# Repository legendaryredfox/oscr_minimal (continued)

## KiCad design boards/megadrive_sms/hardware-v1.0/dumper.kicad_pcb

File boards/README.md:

# boards/ — variantes de hardware

Cada pasta é uma versão mínima de hardware do OSCR, em shield para Arduino Mega 2560 R3, só USB (sem LCD, SD e RTC). Firmware, `host/` e `gui/` (raiz) são comuns; o que muda entre as placas são os slots e a pinagem.

| Pasta | Slots | Estado |
|---|---|---|
| [`16_bits/`](16_bits/) | SNES, Mega Drive | Projeto KiCad derivado da `16_and_8_bits`, 108 × 86 mm. **Versões v1.0, v1.2 (sem TVS) e v1.3 (seletor de tensão, sem TVS nem resistores de 470 Ω), D128, D139 e D140.** Gerbers v. 1.2 (D87: `/CART` no D50, C5 e C6, pontos de teste a 2,54 mm, D99) e v1.0 (a antiga `rev2`: alimentação em 0,8 mm, D97; o zip da v1.0 original, com trilhas de 0,3 mm, saiu do repositório em D110) |
| [`megadrive/`](megadrive/) | Mega Drive | Projeto KiCad criado de `16_bits` (D92), slot no centro, 107 × 65 mm, gerbers v1.1 gerados. **v1.1 com o seletor de tensão 3,3 V/5 V (D138).** Nada encomendado |
| [`snes/`](snes/) | SNES | Projeto KiCad criado de `16_bits` (D93), PIC12F629 em soquete, 107 × 65 mm, só a v1.0 (o SA-1 precisa de 5 V: sem seletor). Nada encomendado |
| [`nes/`](nes/) | NES | Projeto KiCad criado da `16_and_8_bits` (D95), Si5351 sem PIC, 110 × 65 mm, gerbers v1.1 gerados. Famicom em `famicom/` ou `famicom_nes/`. **v1.1 com o seletor de tensão 3,3 V/5 V (D138).** Nada encomendado |
| [`famicom/`](famicom/) | Famicom | Projeto KiCad criado da `16_and_8_bits` (D98), sem Si5351 nem PIC, 107 × 65 mm, gerbers v1.1 gerados. **v1.1 com o seletor de tensão 3,3 V/5 V (D138).** Nada encomendado |
| [`famicom_nes/`](famicom_nes/) | Famicom e NES | Projeto KiCad criado da `16_and_8_bits` (D100), Si5351 sem PIC, 117 × 79 mm (D124), gerbers v1.1 gerados. **v1.1 com o seletor de tensão 3,3 V/5 V (D138).** Nada encomendado |
| [`16_and_8_bits/`](16_and_8_bits/) | SNES, NES, Famicom, Mega Drive, GBA | Projeto KiCad pronto, 144 × 118 mm (v1.0, mínima com fusível) e 144 × 134 mm (**v1.1 com o seletor de tensão 3,3 V/5 V nos slots NES, Famicom e Mega Drive**, D157). Nada encomendado |
| [`megadrive_sms/`](megadrive_sms/) | Mega Drive, Master System | Projeto KiCad criado da `megadrive` v1.0 (D136), 107,1 × 83,1 mm, **v1.0 sem o bloco de troca**, gerbers v1.0 gerados. Nada encomendado. Pendências: direção da etiqueta do SMS, núcleo SMS no firmware |
| [`8_bits/`](8_bits/) | NES, Famicom, Master System | Projeto KiCad criado da `famicom_nes` com o slot SMS da `megadrive_sms` (D153), 117,1 × 97,1 mm (v1.0, mínima com fusível) e 117,1 × 109,1 mm (v1.1, com o seletor de tensão). Nada encomendado |
| [`gb_gba/`](gb_gba/) | GBA; GB e GBC por adaptador | Projeto KiCad criado de `16_and_8_bits` (D94), 138 × 67 mm, gerbers v1.0 gerados. Nada encomendado |
| [`n64/`](n64/) | N64 | Projeto KiCad criado da `16_and_8_bits` (D121), 3,3 V, Si5351 só para a EEPROM, 110,1 × 65,1 mm, só a v1.0 (placa de 3,3 V: sem seletor). Nada encomendado |
| [`completa/`](completa/) | SNES, NES, Famicom, Mega Drive, Master System, N64 e GBA | Projeto KiCad criado da `16_and_8_bits` com os slots SMS e N64 acrescentados (D156), 144,2 × 152,2 mm (v1.0, mínima com fusível) e 144,2 × 168,2 mm (v1.1, com o seletor de tensão nos slots de 5 V, menos o SNES). O N64 está desligado no firmware. Nada encomendado |
| [`_lib/`](_lib/) | Símbolos e footprints compartilhados | Em uso por todas as placas com projeto KiCad |

Cada placa com projeto tem um `render.png` (render 3D do KiCad, vista de cima, da versão mais nova) e, **dentro da pasta de cada versão** (`hardware-v1.0/` etc.), `render-cima.png` e `render-baixo.png` (1768 × 1064, print do render 3D do KiCad) ao lado do `README.md` da versão; refazer com `tools/render_board.sh <placa> <versões...>` e `docs/componentes-opcionais.md`: peças que podem ficar sem montar, o que deixa de funcionar e quais cartuchos são afetados.

## Troca de cartucho, F1 e seletor de tensão (D138, D139)

O 5V dos slots **não é cortado por software** em nenhuma placa: o bloco de troca de cartucho (Q1, Q2, Q3, LEDs verde e amarelo, D19 e D53; D126 a D128) foi retirado em D139. Para trocar o cartucho, **desligue o USB**. Ficaram o F1 (suporte de fusível 5×20 mm de 500 mA, em todas as versões), e nas v1.1 com slot de 5 V o seletor 3,3 V/5 V, o jumper J1 "TRAVA 3,3 V" e os resistores de 470 Ω em série. Circuito e peças: [`docs/referencia/seletor-tensao.md`](../docs/referencia/seletor-tensao.md).

## Como os esquemáticos são desenhados

Para leitura humana (D122): os circuitos locais (LED, resistores, capacitores, Si5351, PIC, regulador, pull-ups) têm **fios diretos** entre os pinos; a alimentação usa **símbolos** `+5V`, `+3V3`, `+5V_CART` e `GND`; **rótulos de net só nos barramentos longos** entre o Mega e os slots. As folhas são geradas por `tools/sch/regen.py` (preserva peças, referências e UUIDs, só refaz o desenho); `tools/sch/verify.py` confere que a conectividade ficou idêntica e `tools/sch/sync_names.py` alinha os nomes de net do PCB (a geometria não muda).

## Layout de cada variante

```
boards/<variante>/
├── README.md        # slots, estado, decisões próprias
├── hardware-v1.0/   # uma pasta por versão (hardware-v1.1/ ...): projeto KiCad (dumper.kicad_pro/_sch/_pcb, fp-lib-table, sym-lib-table) e README.md da versão
├── fab/             # por versão: gerbers-<versão>/, bom-<versão>.csv e dumper-<versão>-jlcpcb.zip
└── docs/            # pinmap.md, bom.md, montagem.md da variante
```

As tabelas de bibliotecas apontam para `${KIPRJMOD}/../../_lib/`. Pinagem idêntica ao OSCR HW5 continua regra de ouro (`CLAUDE.md`, seção 3). Uma variante nova nasce copiando o esqueleto e gerando o próprio `docs/pinmap.md`; `tools/check_netlist.py` aceita `--board <pasta>` e `tools/export_fab.sh <pasta> <versão>` gera os arquivos da fábrica; `gen_pinmap.py` e os demais scripts gerais de `tools/` apontam para `16_and_8_bits/`. As placas de um sistema só têm scripts próprios em `tools/<placa>/` (receita completa em `boards/nes/README.md` e na D96).

Todas as placas novas (`megadrive`, `snes`, `nes`, `famicom`, `famicom_nes`, `gb_gba`, `n64`) e as v1.1 foram roteadas por autoroteador (na v1.1, o roteamento inteiro foi refeito) e **não foram revisadas à mão no KiCad**; nenhuma foi encomendada, montada ou testada com cartucho.

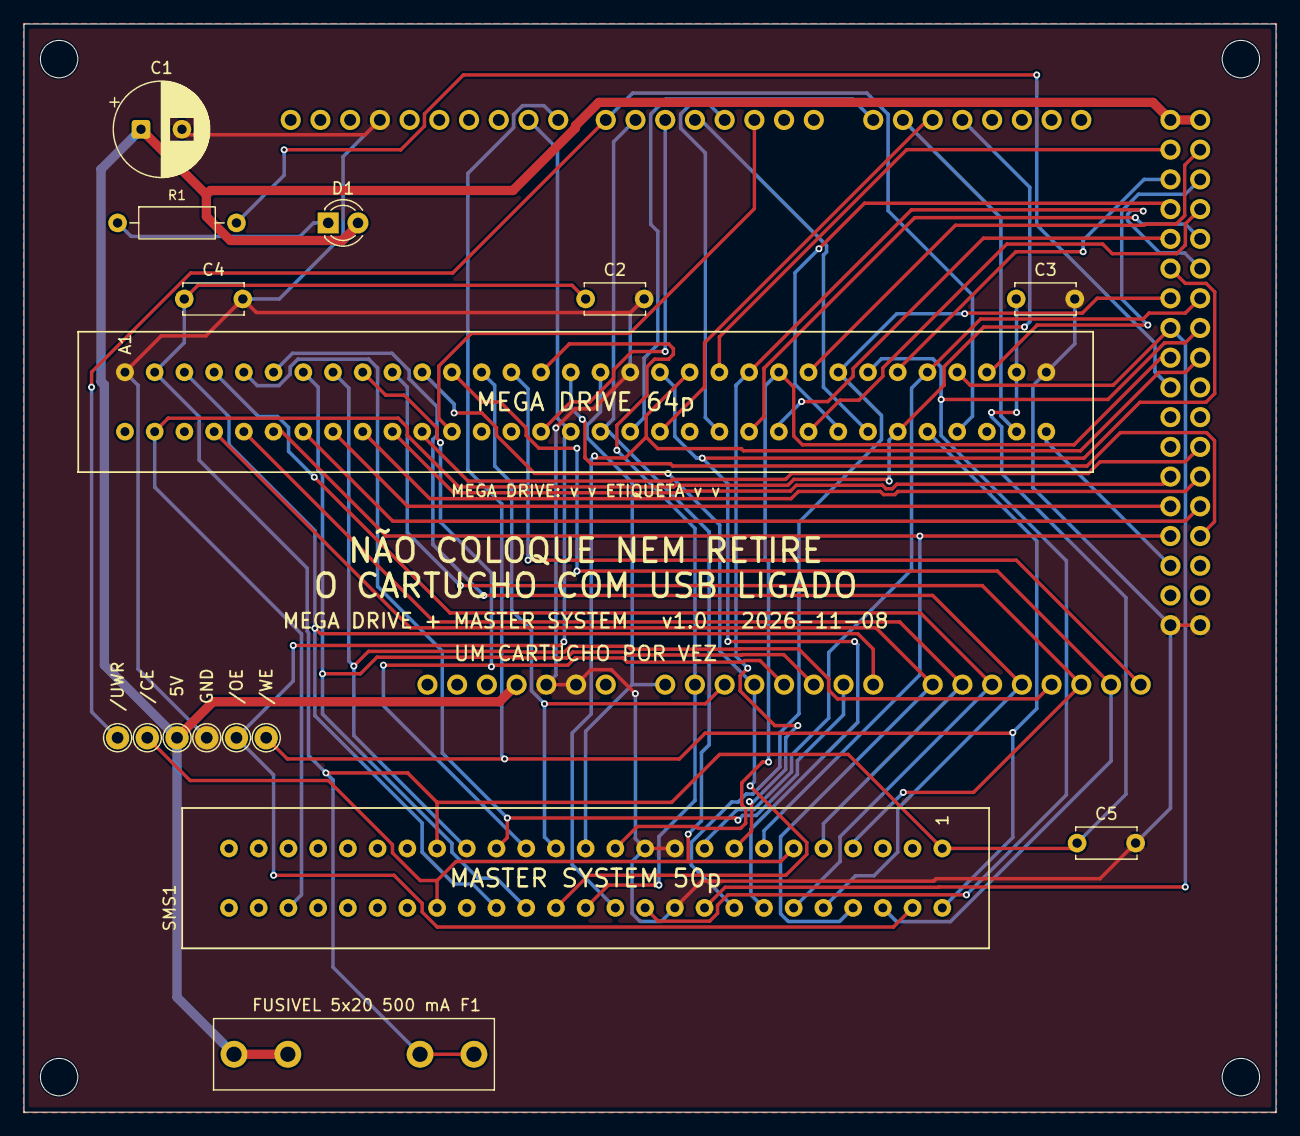
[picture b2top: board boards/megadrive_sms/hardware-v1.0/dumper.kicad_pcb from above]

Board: 2 copper layers, 107.0 x 93.0 mm, 21 parts (0 on the bottom side), 57 nets.

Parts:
A1: Mega2560_R3_Shield
C1: 470u/16V; CP_Radial_D8.0mm_P3.50mm
C2, C3, C4, C5: 100n; C_Disc_D5.0mm_W2.5mm_P5.00mm
D1: LED 3mm; LED_D3.0mm
F1: Fusivel 5x20 500mA; Fuseholder_Littelfuse_100_series_5x20mm
MD1: MD_Slot
MH1, MH2, MH5, MH6: MountingHole_3.2mm; MountingHole_3.2mm_M3
R1: 220R; R_Axial_DIN0207_L6.3mm_D2.5mm_P10.16mm_Horizontal
SMS1: SMS_Slot
TP1: 5V; TestPoint_THTPad_D2.0mm_Drill1.0mm
TP2: GND; TestPoint_THTPad_D2.0mm_Drill1.0mm
TP3: /CE; TestPoint_THTPad_D2.0mm_Drill1.0mm
TP4: /OE; TestPoint_THTPad_D2.0mm_Drill1.0mm
TP5: /WE; TestPoint_THTPad_D2.0mm_Drill1.0mm
TP6: /UWR; TestPoint_THTPad_D2.0mm_Drill1.0mm

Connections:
+5V: A1.5V1, A1.5V3, A1.5V4, C1.1, D1.2, F1.1, TP1.1
+5V_CART: C2.1, C3.1, C4.1, C5.1, F1.2, MD1.A2, MD1.A31, SMS1.1, SMS1.35
/A0: A1.A0, MD1.A17, SMS1.25
/A1: A1.A1, MD1.A15, SMS1.26
/A2: A1.A2, MD1.A13, SMS1.27
/A3: A1.A3, MD1.A11, SMS1.28
/A4: A1.A4, MD1.A9, SMS1.29
/A5: A1.A5, MD1.A7, SMS1.30
/A6: A1.A6, MD1.A5, SMS1.31
/A7: A1.A7, MD1.A3, SMS1.32
/A8: A1.A8, MD1.B4, SMS1.8
/A9: A1.A9, MD1.B5, SMS1.9
/A10: A1.A10, MD1.A4, SMS1.12
/A11: A1.A11, MD1.A6, SMS1.10
/A12: A1.A12, MD1.A8, SMS1.33
/A13: A1.A13, MD1.A10, SMS1.7
/A14: A1.A14, MD1.A12, SMS1.6
/A15: A1.A15, MD1.A14
/CART: A1.D50, MD1.B32
/D2: A1.D2, MD1.B12
/D3: A1.D3, MD1.B21
/D4: A1.D4, MD1.B26
/D5: A1.D5, MD1.B15
/D6: A1.D6, MD1.B17, SMS1.11, SMS1.36, TP3.1
/D7: A1.D7, MD1.B29, TP6.1
/D8: A1.D8, MD1.B28, SMS1.2, TP5.1
/D9: A1.D9, MD1.B16, SMS1.4, TP4.1
/D14: A1.D14, MD1.B18
/D15: A1.D15, MD1.B31
/D16: A1.D16, MD1.B19
/D17: A1.D17, MD1.B2, MD1.B27, SMS1.46
/D22: A1.D22, MD1.A21
/D23: A1.D23, MD1.A24
/D24: A1.D24, MD1.A27
/D25: A1.D25, MD1.A30
/D26: A1.D26, MD1.B25
/D27: A1.D27, MD1.B24
/D28: A1.D28, MD1.B23
/D29: A1.D29, MD1.B22
/D30: A1.D30, MD1.A19, SMS1.14
/D31: A1.D31, MD1.A22, SMS1.15
/D32: A1.D32, MD1.A25, SMS1.16
/D33: A1.D33, MD1.A28, SMS1.17
/D34: A1.D34, MD1.A29, SMS1.18
/D35: A1.D35, MD1.A26, SMS1.22
/D36: A1.D36, MD1.A23, SMS1.23
/D37: A1.D37, MD1.A20, SMS1.24
/D43: A1.D43, MD1.B11
/D44: A1.D44, MD1.B10
/D45: A1.D45, MD1.B9
/D46: A1.D46, MD1.B8
/D47: A1.D47, MD1.B7
/D48: A1.D48, MD1.B6, SMS1.13
/D49: A1.D49, MD1.A16
GND: A1.GND1, A1.GND2, A1.GND3, A1.GND5, A1.GND6, C1.2, C2.2, C3.2, C4.2, C5.2, MD1.A1, MD1.A18, MD1.A32, SMS1.19, SMS1.20, SMS1.21, TP2.1
unnamed: A1.D38, R1.2
unnamed: D1.1, R1.1

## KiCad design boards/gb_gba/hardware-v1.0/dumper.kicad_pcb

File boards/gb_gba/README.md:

# gb_gba — GBA; GB e GBC por adaptador

**README por versão** (renders de cima e de baixo, peças, diferenças): [v1.0](hardware-v1.0/README.md).

Versão mínima de uma função: um slot **GBA** (32 pads SMD, 1,5 mm, **3,3 V**) em shield para Arduino Mega 2560 R3, só USB. GB e GBC entram **só pelo slot GBA, com adaptador** (D56). Um cartucho por vez. Pinagem idêntica ao OSCR HW5 (`docs/pinmap.md`, recorte da `16_and_8_bits`). Sem SD, sem LCD, sem Si5351 e sem PIC.

**Estado:** v1.0, 138,1 × 67,1 mm. ERC com 1 aviso de biblioteca (U1, antes U3; o mesmo da `16_and_8_bits`); DRC sem erros nem ligações abertas (só avisos de biblioteca e paridade); netlist confere com `docs/pinmap.md`; gerbers em `fab/`. Roteada pelo Freerouting (MCP) com o GND junto; o `/D9` o autoroteador não achou caminho em nenhuma tentativa e foi roteado pelo A* de `tools/historico/pcb_v12` (`tools/boards/gb_gba/route_net.py`). **Revisar o layout no KiCad antes de encomendar.** Nada encomendado nem montado. Montagem: `docs/montagem.md`. Trilhas de alimentação (`+5V`, `+3V3`) alargadas até onde cabe, 0,8 mm na maior parte (`tools/historico/revisao/widen_power.py`, D96).

## Diferenças em relação à `16_and_8_bits`

| Item | 16_and_8_bits | gb_gba |
|---|---|---|
| Slots | SNES, NES, Famicom, Mega Drive, GBA | só GBA |
| Regulador 3,3 V (U3, C7, C8, C9; na gb_gba: U1, C2, C3, C4, D109) | sim | sim |
| Si5351, PIC, R2, C2 a C6 | sim | não |
| Placa | 144 × 108 mm | 138,1 × 67,1 mm |
| Furos | 4 M3 de canto, 6 do Mega, 2 M2 do Si5351 | 4 M3 junto ao Mega (nenhum do lado do slot GBA); sem os 6 do Mega |

O slot GBA ficou **na mesma orientação** (boca para a direita, etiqueta para cima), mas encostado no Mega, com as peças soltas dentro da área do Mega. O pino 31 (AUD_IRQ) continua sem ligação (D22).

## Como foi feita

Mesma receita da `megadrive/` e da `snes/` (`boards/megadrive/README.md`, D92 e D93), com `tools/boards/gb_gba/place.py`. `fix_nets.py` leva **um pad por chamada** (num laço de shell).

```
python3 tools/check_netlist.py --board gb_gba
kicad-cli sch erc boards/gb_gba/hardware-v1.0/dumper.kicad_sch
kicad-cli pcb drc boards/gb_gba/hardware-v1.0/dumper.kicad_pcb
tools/export_fab.sh gb_gba v1.0
```

**Peças opcionais:** o que se perde ao retirar cada componente, e que jogos são afetados, está em [`docs/componentes-opcionais.md`](docs/componentes-opcionais.md).

## Versões

Só a **v1.0** (`hardware-v1.0/`; fábrica em `fab/gerbers-v1.0/`, `fab/dumper-v1.0-jlcpcb.zip`, `fab/bom-v1.0.csv`; renders em `hardware-v1.0/render-cima.png` e `render-baixo.png`). Ela já leva o suporte do fusível F1 (D138). O 5V dos slots vai direto do Mega e **não é cortado por software** (o bloco de troca de cartucho, D126 a D128, foi retirado em D139): para trocar o cartucho, desligue o USB. Verificação: `python3 tools/check_netlist.py --board gb_gba`.

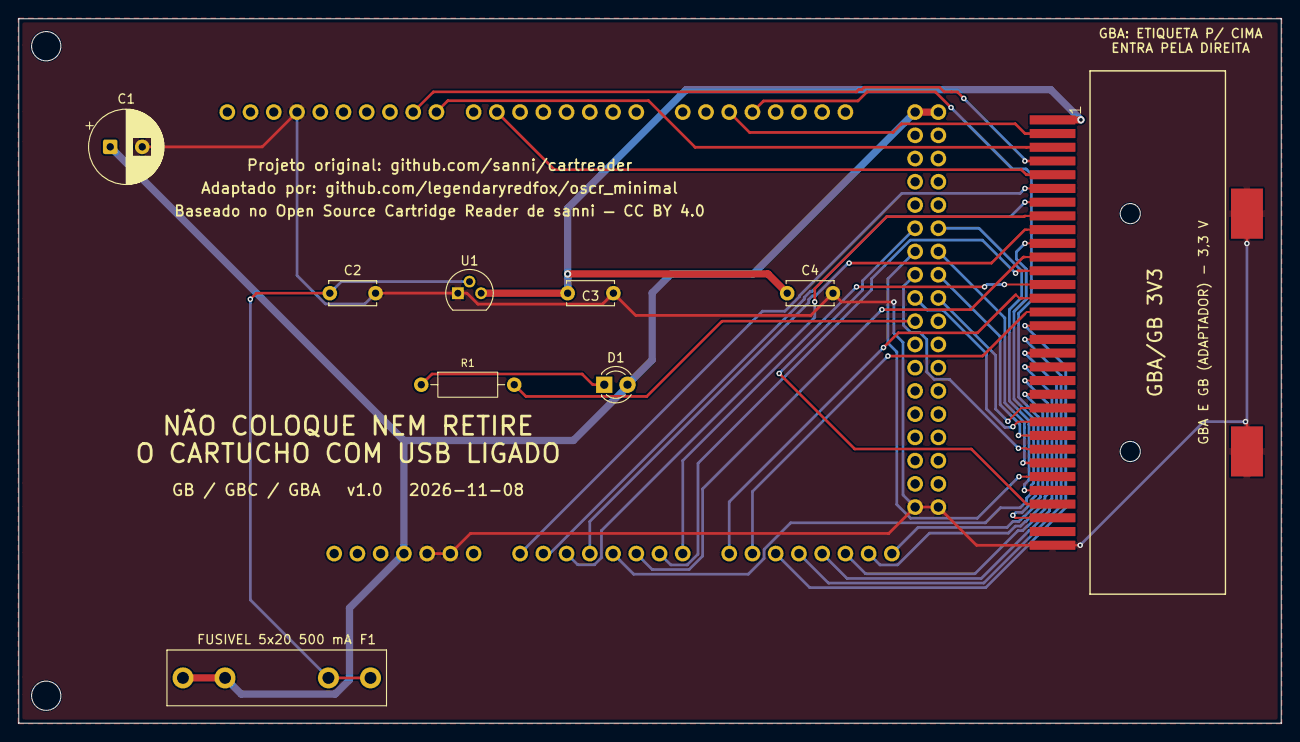
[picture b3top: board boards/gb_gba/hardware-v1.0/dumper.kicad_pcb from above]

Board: 2 copper layers, 138.0 x 77.0 mm, 12 parts (0 on the bottom side), 35 nets.

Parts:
A1: Mega2560_R3_Shield
C1: 470u/16V; CP_Radial_D8.0mm_P3.50mm
C2, C3: 1u; C_Disc_D5.0mm_W2.5mm_P5.00mm
C4: 100n; C_Disc_D5.0mm_W2.5mm_P5.00mm
D1: LED 3mm; LED_D3.0mm
F1: Fusivel 5x20 500mA; Fuseholder_Littelfuse_100_series_5x20mm
GBA1: GBA_Slot
MH1, MH3: MountingHole_3.2mm; MountingHole_3.2mm_M3
R1: 220R; R_Axial_DIN0207_L6.3mm_D2.5mm_P10.16mm_Horizontal
U1: MCP1700-3302E/TO (3,3 V); TO-92

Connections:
+3V3: C3.1, C4.1, GBA1.1, U1.3
+5V: A1.5V1, A1.5V3, A1.5V4, C1.1, D1.2, F1.1
+5V_CART: C2.1, F1.2, U1.2
/A0: A1.A0, GBA1.6
/A1: A1.A1, GBA1.7
/A2: A1.A2, GBA1.8
/A3: A1.A3, GBA1.9
/A4: A1.A4, GBA1.10
/A5: A1.A5, GBA1.11
/A6: A1.A6, GBA1.12
/A7: A1.A7, GBA1.13
/A8: A1.A8, GBA1.14
/A9: A1.A9, GBA1.15
/A10: A1.A10, GBA1.16
/A11: A1.A11, GBA1.17
/A12: A1.A12, GBA1.18
/A13: A1.A13, GBA1.19
/A14: A1.A14, GBA1.20
/A15: A1.A15, GBA1.21
/D6: A1.D6, GBA1.5
/D8: A1.D8, GBA1.3
/D9: A1.D9, GBA1.4
/D16: A1.D16, GBA1.2
/D17: A1.D17, GBA1.30
/D30: A1.D30, GBA1.29
/D31: A1.D31, GBA1.28
/D32: A1.D32, GBA1.27
/D33: A1.D33, GBA1.26
/D34: A1.D34, GBA1.25
/D35: A1.D35, GBA1.24
/D36: A1.D36, GBA1.23
/D37: A1.D37, GBA1.22
GND: A1.GND1, A1.GND2, A1.GND3, A1.GND5, A1.GND6, C1.2, C2.2, C3.2, C4.2, GBA1.32, GBA1.SHIELD_3, GBA1.SHIELD_4, U1.1
unnamed: A1.D38, R1.2
unnamed: D1.1, R1.1

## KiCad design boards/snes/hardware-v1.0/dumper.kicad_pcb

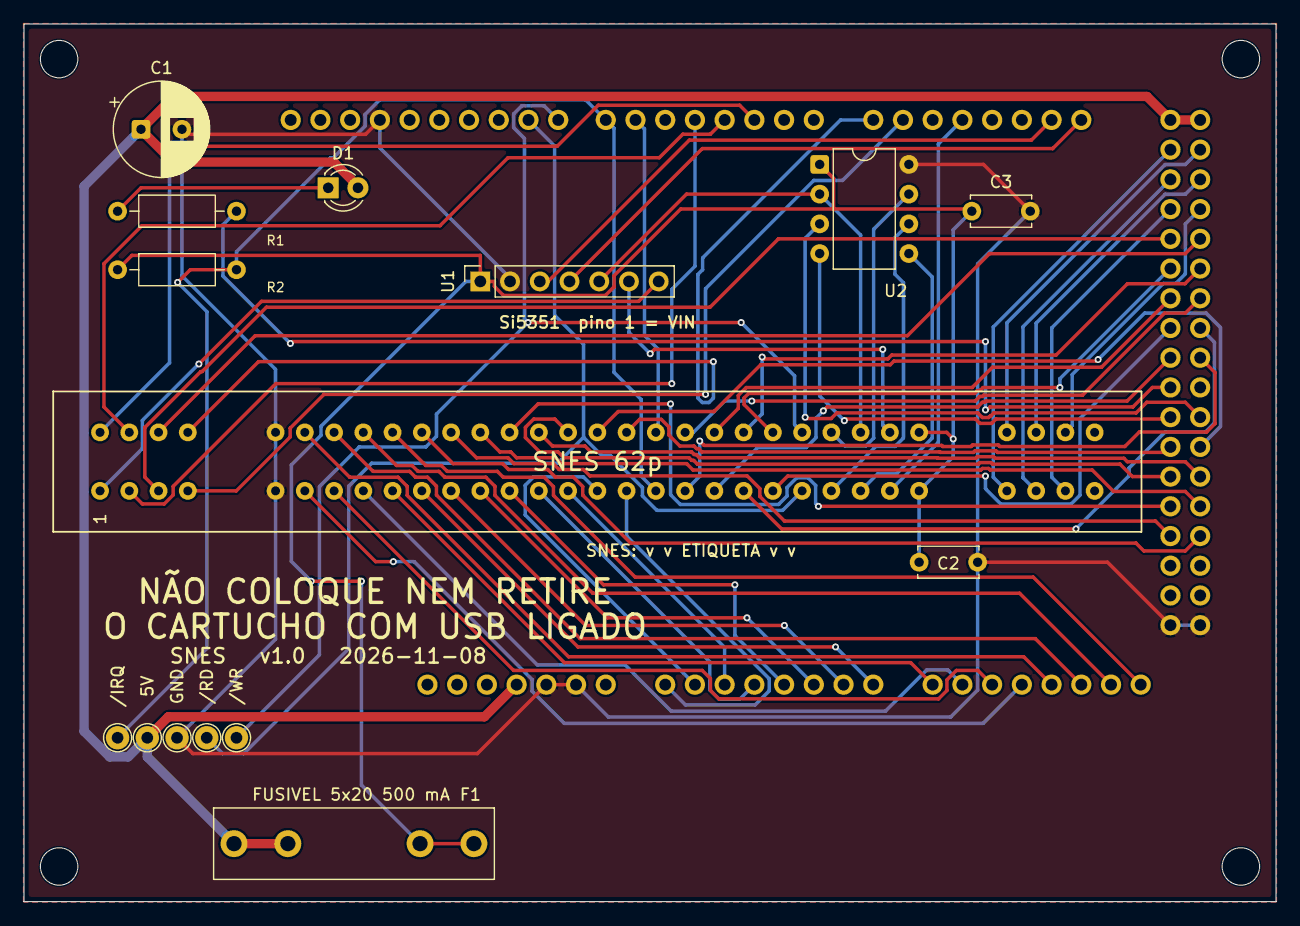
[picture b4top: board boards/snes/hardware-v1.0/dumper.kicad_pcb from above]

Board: 2 copper layers, 107.0 x 75.0 mm, 20 parts (0 on the bottom side), 65 nets.

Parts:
A1: Mega2560_R3_Shield
C1: 470u/16V; CP_Radial_D8.0mm_P3.50mm
C2, C3: 100n; C_Disc_D5.0mm_W2.5mm_P5.00mm
D1: LED 3mm; LED_D3.0mm
F1: Fusivel 5x20 500mA; Fuseholder_Littelfuse_100_series_5x20mm
MH1, MH2, MH3, MH4: MountingHole_3.2mm; MountingHole_3.2mm_M3
R1: 220R; R_Axial_DIN0207_L6.3mm_D2.5mm_P10.16mm_Horizontal
R2: 1k; R_Axial_DIN0207_L6.3mm_D2.5mm_P10.16mm_Horizontal
SNES1: SNES_Slot
TP1: 5V; TestPoint_THTPad_D2.0mm_Drill1.0mm
TP2: GND; TestPoint_THTPad_D2.0mm_Drill1.0mm
TP3: /RD; TestPoint_THTPad_D2.0mm_Drill1.0mm
TP4: /WR; TestPoint_THTPad_D2.0mm_Drill1.0mm
TP5: /IRQ; TestPoint_THTPad_D2.0mm_Drill1.0mm
U1: Si5351_Module; PinSocket_1x07_P2.54mm_Vertical
U2: PIC12F629 (em soquete; snescic-lock-resync); DIP-8_W7.62mm

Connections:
+5V: A1.5V1, A1.5V3, A1.5V4, C1.1, D1.2, F1.1, TP1.1
+5V_CART: C2.1, C3.1, F1.2, R2.1, SNES1.27, SNES1.58, U1.1, U2.1
/A0: A1.A0, SNES1.17
/A1: A1.A1, SNES1.16
/A2: A1.A2, SNES1.15
/A3: A1.A3, SNES1.14
/A4: A1.A4, SNES1.13
/A5: A1.A5, SNES1.12
/A6: A1.A6, SNES1.11
/A7: A1.A7, SNES1.10
/A8: A1.A8, SNES1.9
/A9: A1.A9, SNES1.8
/A10: A1.A10, SNES1.7
/A11: A1.A11, SNES1.6
/A12: A1.A12, SNES1.37
/A13: A1.A13, SNES1.38
/A14: A1.A14, SNES1.39
/A15: A1.A15, SNES1.40
/CIC_DATA_0: SNES1.55, U2.7
/CIC_DATA_1: SNES1.24, U2.6
/CIC_RESET: SNES1.25, U2.5
/CLK0: SNES1.1, U1.7
/CLK1: SNES1.57, U1.6
/CLK2: SNES1.56, U1.5, U2.2
/D2: A1.D2, SNES1.32
/D3: A1.D3, SNES1.33
/D4: A1.D4, SNES1.2
/D6: A1.D6, SNES1.49
/D7: A1.D7, R2.2, SNES1.18, TP5.1
/D8: A1.D8, SNES1.54, TP4.1
/D9: A1.D9, SNES1.23, TP3.1
/D14: A1.D14, SNES1.35
/D15: A1.D15, SNES1.4
/D17: A1.D17, SNES1.26
/D22: A1.D22, SNES1.28
/D23: A1.D23, SNES1.59
/D24: A1.D24, SNES1.29
/D25: A1.D25, SNES1.60
/D26: A1.D26, SNES1.30
/D27: A1.D27, SNES1.61
/D28: A1.D28, SNES1.3
/D29: A1.D29, SNES1.34
/D30: A1.D30, SNES1.53
/D31: A1.D31, SNES1.52
/D32: A1.D32, SNES1.51
/D33: A1.D33, SNES1.50
/D34: A1.D34, SNES1.22
/D35: A1.D35, SNES1.21
/D36: A1.D36, SNES1.20
/D37: A1.D37, SNES1.19
/D42: A1.D42, SNES1.48
/D43: A1.D43, SNES1.47
/D44: A1.D44, SNES1.46
/D45: A1.D45, SNES1.45
/D46: A1.D46, SNES1.44
/D47: A1.D47, SNES1.43
/D48: A1.D48, SNES1.42
/D49: A1.D49, SNES1.41
GND: A1.GND1, A1.GND2, A1.GND3, A1.GND5, A1.GND6, C1.2, C2.2, C3.2, SNES1.5, SNES1.36, TP2.1, U1.2, U2.8
unnamed: A1.D38, R1.2
unnamed: D1.1, R1.1
unnamed: A1.D21, U1.4
unnamed: A1.D20, U1.3
unnamed: A1.D40, U2.4
unnamed: A1.D41, U2.3

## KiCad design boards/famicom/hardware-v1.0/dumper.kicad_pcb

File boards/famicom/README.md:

# famicom — só Famicom

**README por versão** (renders de cima e de baixo, peças, diferenças): [v1.0](hardware-v1.0/README.md), [v1.1](hardware-v1.1/README.md).

Versão mínima de uma função: um slot **Famicom** (60p, 2,54 mm) em shield para Arduino Mega 2560 R3, 100% THT, só USB, **5 V** fixo. Um cartucho por vez. Pinagem idêntica ao OSCR HW5 (`docs/pinmap.md`, recorte da `16_and_8_bits`).

**Sem Si5351 e sem PIC:** o slot Famicom não tem pino de clock nem CIC do SNES; o `pinmap.md` não liga nenhum deles ao slot. A placa é a mais simples de todas: slot, LED, C1 e um capacitor.

**Estado:** v1.1, 107,1 × 65,1 mm (v1.0: 107,1 × 61,1 mm). ERC 0 violações; DRC sem erros nem ligações abertas (só 4 avisos de biblioteca e os de paridade das outras placas); netlist confere com `docs/pinmap.md`; gerbers em `fab/`. Roteada pelo Freerouting (MCP) com GND roteado junto e costurado com vias; alimentação (`+5V`) com 0,8 mm desde o roteamento (padrão de net class `/+5V` já corrigido, D96). **Revisar o layout no KiCad antes de encomendar.** Nada encomendado nem montado. Montagem: `docs/montagem.md`.

**NES:** cartucho de 72 pinos não entra aqui; use `boards/nes/`.

## Diferenças em relação à `16_and_8_bits`

| Item | 16_and_8_bits | famicom |
|---|---|---|
| Slots | SNES, NES, Famicom, Mega Drive, GBA | só Famicom |
| Mantido | LED (D1, R1), C1, C4 (VCC do slot; agora C2, D109) | idem |
| Removido | SNES1, NES1, MD1, GBA1, Si5351 (U1), PIC (U2), R2, regulador U3 e C7, C8, C9, C2, C3, C5, C6, furos M2 | |
| Placa | 144 × 108 mm | 107,1 × 65,1 mm |

O slot fica entre as fileiras de pinos do Mega, no mesmo lugar que o Mega Drive na `megadrive/`. **A v1.0 não tem os 6 furos do Mega** (só os 4 de canto) e o F1 fica entre o slot e o header de baixo do Mega, sem a faixa extra: 107,1 × 61,1 mm (D142). Na v1.1, os 6 furos não metalizados do Mega e os 4 de canto foram mantidos.

Ficam sem ligação no Mega: tudo que só os outros sistemas usam (`D2..D9`, `D14..D17`, `D20`, `D21`, `D29..D34`, `D36`, `D37`, `D40`, `D41`) e os de sempre (`D0`, `D1`, `D10..D13`, `D18`, `D19`, `D39`, `D50..D53`).

## Como foi feita

Mesma receita da `nes/` (`boards/nes/README.md`), com `tools/boards/famicom/place.py`: `strip_sch.py` (SNES1, NES1, MD1, GBA1, U1, U2, R2, U3, C2, C3, C5 a C9), `place.py`, `tools/boards/nes/sync_unconnected.py`, `autoroute` do KiCad MCP com o GND como trilha, depois `add_zones.py`, `stitch.py`, `tools/historico/revisao/widen_power.py` (sem efeito aqui: o 5V já saiu com 0,8 mm) e `fill_zones.py`.

```
python3 tools/check_netlist.py --board famicom
kicad-cli sch erc boards/famicom/hardware-v1.1/dumper.kicad_sch
kicad-cli pcb drc boards/famicom/hardware-v1.1/dumper.kicad_pcb
tools/export_fab.sh famicom v1.0
```

**Peças opcionais:** o que se perde ao retirar cada componente, e que jogos são afetados, está em [`docs/componentes-opcionais.md`](docs/componentes-opcionais.md).

## Versões

| Versão | O que tem | Projeto KiCad | Fábrica | Renders (cima e baixo) |
|---|---|---|---|---|
| v1.0 | F1 (suporte de fusível); 5V direto nos slots; 107,1 × 61,1 mm, sem os 6 furos do Mega (D142) | `hardware-v1.0/` | `fab/gerbers-v1.0/`, `fab/dumper-v1.0-jlcpcb.zip`, `fab/bom-v1.0.csv` | `hardware-v1.0/render-cima.png`, `hardware-v1.0/render-baixo.png` |
| v1.1 | v1.0 mais o seletor de tensão 3,3 V/5 V e o J1 (D138; sem resistores em série, D140) | `hardware-v1.1/` | `fab/gerbers-v1.1/`, `fab/dumper-v1.1-jlcpcb.zip`, `fab/bom-v1.1.csv` | `hardware-v1.1/render-cima.png`, `hardware-v1.1/render-baixo.png` (`render.png` = v1.1, de cima) |

O 5V dos slots **não é cortado por software** em nenhuma versão (o bloco de troca de cartucho, D126 a D128, foi retirado em D139): para trocar o cartucho, desligue o USB. Verificação: `python3 tools/check_netlist.py --board famicom` (v1.1) e `python3 tools/check_netlist.py --board famicom boards/famicom/hardware-v1.0/dumper.kicad_sch` (v1.0).

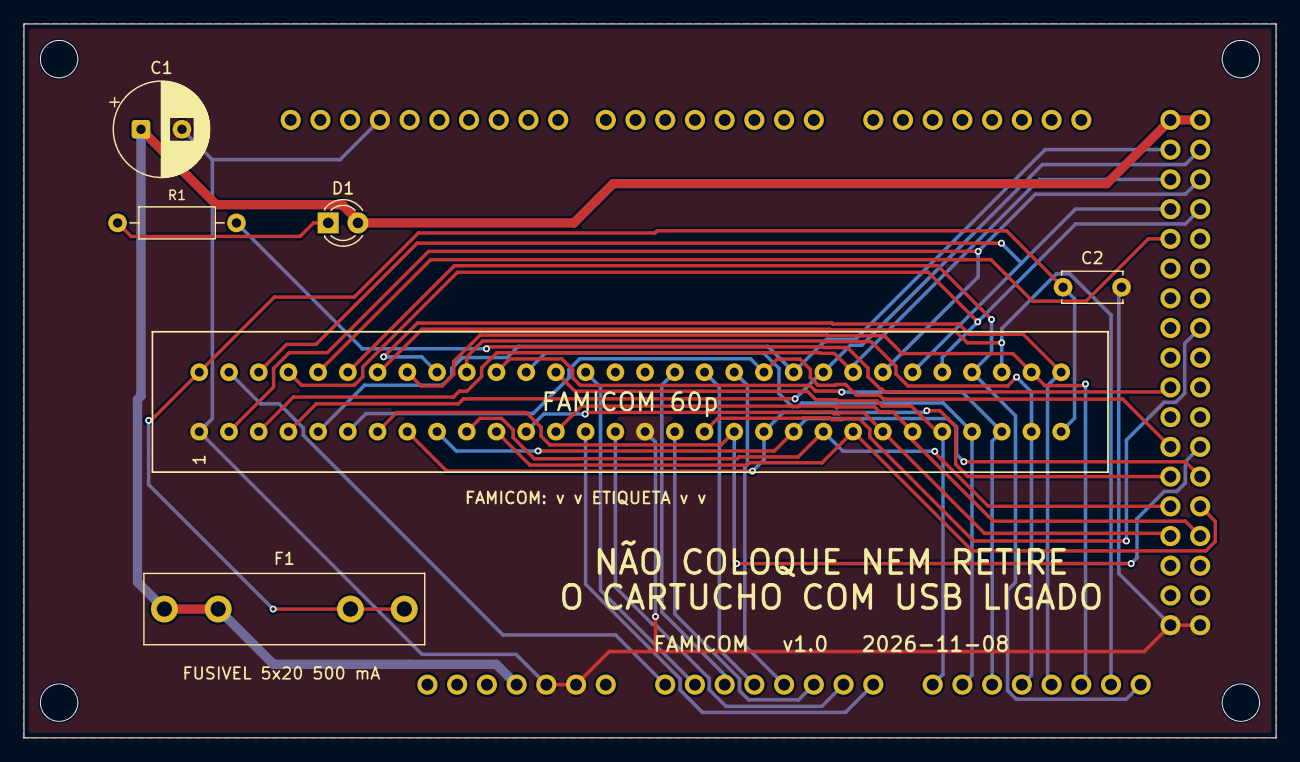
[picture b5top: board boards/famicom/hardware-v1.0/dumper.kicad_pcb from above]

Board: 2 copper layers, 107.0 x 61.0 mm, 11 parts (0 on the bottom side), 37 nets.

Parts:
A1: Mega2560_R3_Shield
C1: 470u/16V; CP_Radial_D8.0mm_P3.50mm
C2: 100n; C_Disc_D5.0mm_W2.5mm_P5.00mm
D1: LED 3mm; LED_D3.0mm
F1: Fusivel 5x20 500mA; Fuseholder_Littelfuse_100_series_5x20mm
FC1: FC_Slot
MH1, MH2, MH3, MH4: MountingHole_3.2mm; MountingHole_3.2mm_M3
R1: 220R; R_Axial_DIN0207_L6.3mm_D2.5mm_P10.16mm_Horizontal

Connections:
+5V: A1.5V1, A1.5V3, A1.5V4, C1.1, D1.2, F1.1
+5V_CART: C2.1, F1.2, FC1.30, FC1.31
/A0: A1.A0, FC1.32
/A1: A1.A1, FC1.44
/A2: A1.A2, FC1.47
/A3: A1.A3, FC1.48
/A4: A1.A4, FC1.49
/A5: A1.A5, FC1.17
/A6: A1.A6, FC1.15
/A7: A1.A7, FC1.14
/A8: A1.A8, FC1.26, FC1.43
/A9: A1.A9, FC1.27, FC1.42
/A10: A1.A10, FC1.28, FC1.41
/A11: A1.A11, FC1.29, FC1.40
/A12: A1.A12, FC1.39, FC1.60
/A13: A1.A13, FC1.38, FC1.59
/A14: A1.A14, FC1.37, FC1.58
/A15: A1.A15, FC1.36, FC1.57
/D22: A1.D22, FC1.5, FC1.51
/D23: A1.D23, FC1.4, FC1.52
/D24: A1.D24, FC1.3, FC1.53
/D25: A1.D25, FC1.2, FC1.54
/D26: A1.D26, FC1.33, FC1.55
/D27: A1.D27, FC1.34, FC1.56
/D28: A1.D28, FC1.35
/D35: A1.D35, FC1.18
/D42: A1.D42, FC1.6, FC1.50
/D43: A1.D43, FC1.7, FC1.19
/D44: A1.D44, FC1.8, FC1.20
/D45: A1.D45, FC1.9, FC1.21
/D46: A1.D46, FC1.10, FC1.22
/D47: A1.D47, FC1.11, FC1.23
/D48: A1.D48, FC1.12, FC1.24
/D49: A1.D49, FC1.13, FC1.25
GND: A1.GND1, A1.GND2, A1.GND3, A1.GND5, A1.GND6, C1.2, C2.2, FC1.1, FC1.16
unnamed: A1.D38, R1.2
unnamed: D1.1, R1.1

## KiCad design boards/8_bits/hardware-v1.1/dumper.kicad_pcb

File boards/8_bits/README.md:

# 8_bits — NES, Famicom e Master System

**README por versão** (renders de cima e de baixo, peças, diferenças): [v1.0](hardware-v1.0/README.md), [v1.1](hardware-v1.1/README.md).

Versão mínima de três slots em shield para Arduino Mega 2560 R3, 100% THT, só USB: **NES** (72p, 2,5 mm), **Famicom** (60p, 2,54 mm) e **Master System / Mark III** (50p, 2,54 mm). Os três slots ficam **em paralelo** nos mesmos pinos do Mega (como no `six_slot_adapter` do OSCR): **um cartucho por vez, em um slot só**. Pinagem idêntica ao OSCR HW5 (`docs/pinmap.md`: NES e Famicom da `famicom_nes`, Master System da `megadrive_sms`).

**Si5351, sem PIC:** o NES usa o `CLK0` do Si5351 no pino 37; Famicom e Master System não usam clock (o pino 47 do SMS fica sem ligação, D136). Sem PIC (CIC do SNES), sem R2 e sem regulador de 3,3 V fixo.

## Versões (regra do usuário, 2026-11-11)

- **v1.0: a mínima que funciona, com fusível.** 5V direto nos slots, atrás do F1 (suporte de fusível 5×20 mm de 500 mA, D144). 117,1 × 97,1 mm.
- **v1.1: proteção mais robusta.** A v1.0 mais o seletor de tensão 3,3 V/5 V nos três slots (LDO LD1117V33, Q1 de bypass, Q2 de comando pelo D18; D138, D147) e o J1 "TRAVA 3,3 V". 117,1 × 109,1 mm. Firmware: ambiente `SerialASCII_Volt`.

O 5V dos slots **não é cortado por software** em nenhuma versão (D139): para trocar o cartucho, desligue o USB.

**Estado:** ERC 0 violações; DRC sem ligações abertas nem erros (só avisos de biblioteca); netlist confere com `docs/pinmap.md` nas duas versões (`tools/check_netlist.py --board 8_bits`). Roteadas pelo Freerouting e costuradas com vias de GND: **revisar o layout no KiCad antes de encomendar**. Nada encomendado, montado nem testado.

## Como foi feita (D153)

Criada da `famicom_nes` (v1.0 para a v1.0, v1.1 para a v1.1) com o slot SMS acrescentado, a mesma receita da `megadrive_sms` (D136). Scripts em `tools/boards/8_bits/` (da raiz do repositório):

1. `add_sms_sch.py` acrescenta SMS1 e o capacitor do slot ao esquemático, tira as marcas de não conexão dos 11 pinos do Mega que só o SMS usa (D6, D8, D9, D17, D30 a D34, D36, D37) e põe os rótulos. Variáveis `SMS_VCC` (`+5V_CART` na v1.0, `VCC_CART` na v1.1), `SMS_CAP` e `SMS_CAP_SRC`.
2. `place_sms.py` (python com `pcbnew`) tira trilhas e zonas, acrescenta SMS1 e o capacitor, liga os pads do Mega às nets novas; na v1.0 estende a placa para baixo (127 para 135 mm).
3. `renum.py` (v1.1) e `renum_pwr.py` deixam as referências em sequência: C4 (SMS), C5 e C6 (LDO), R2 a R4, Q1 e Q2, e os `#PWR` (D109, D150).
4. `reroute.sh` (`VER=v1.0|v1.1`): Freerouting, zonas de GND, costura e preenchimento; depois `tools/troca/pads_solidos.py` onde o DRC acusa `starved_thermal`.

```
python3 tools/check_netlist.py --board 8_bits                                              # v1.1
python3 tools/check_netlist.py --board 8_bits boards/8_bits/hardware-v1.0/dumper.kicad_sch  # v1.0
kicad-cli sch erc boards/8_bits/hardware-v1.1/dumper.kicad_sch
kicad-cli pcb drc boards/8_bits/hardware-v1.1/dumper.kicad_pcb
tools/export_fab.sh 8_bits v1.1
```

## Pendências

1. **Direção da etiqueta do cartucho SMS** no silk (não confirmada; NES e Famicom estão).
2. Medidas dos três slots comprados e do módulo Si5351; folga entre o SMS e os furos de canto de baixo (v1.0: 0,3 mm de folga de caixa).
3. **Firmware:** o núcleo `SMS.cpp` está ligado no fork (D137) mas nunca rodou em hardware; o slot SMS desta placa é o `--mapper 0`.
4. Revisar o layout no KiCad (autoroteador).
5. Sem furos de fixação no Mega (só os 4 de canto): a força de inserir o cartucho passa pelos pinos dos headers.

**Peças opcionais:** [`docs/componentes-opcionais.md`](docs/componentes-opcionais.md). BOM: [`docs/bom.md`](docs/bom.md). Montagem: [`docs/montagem.md`](docs/montagem.md).

Atribuição: baseado no Open Source Cartridge Reader de sanni (CC BY 4.0).

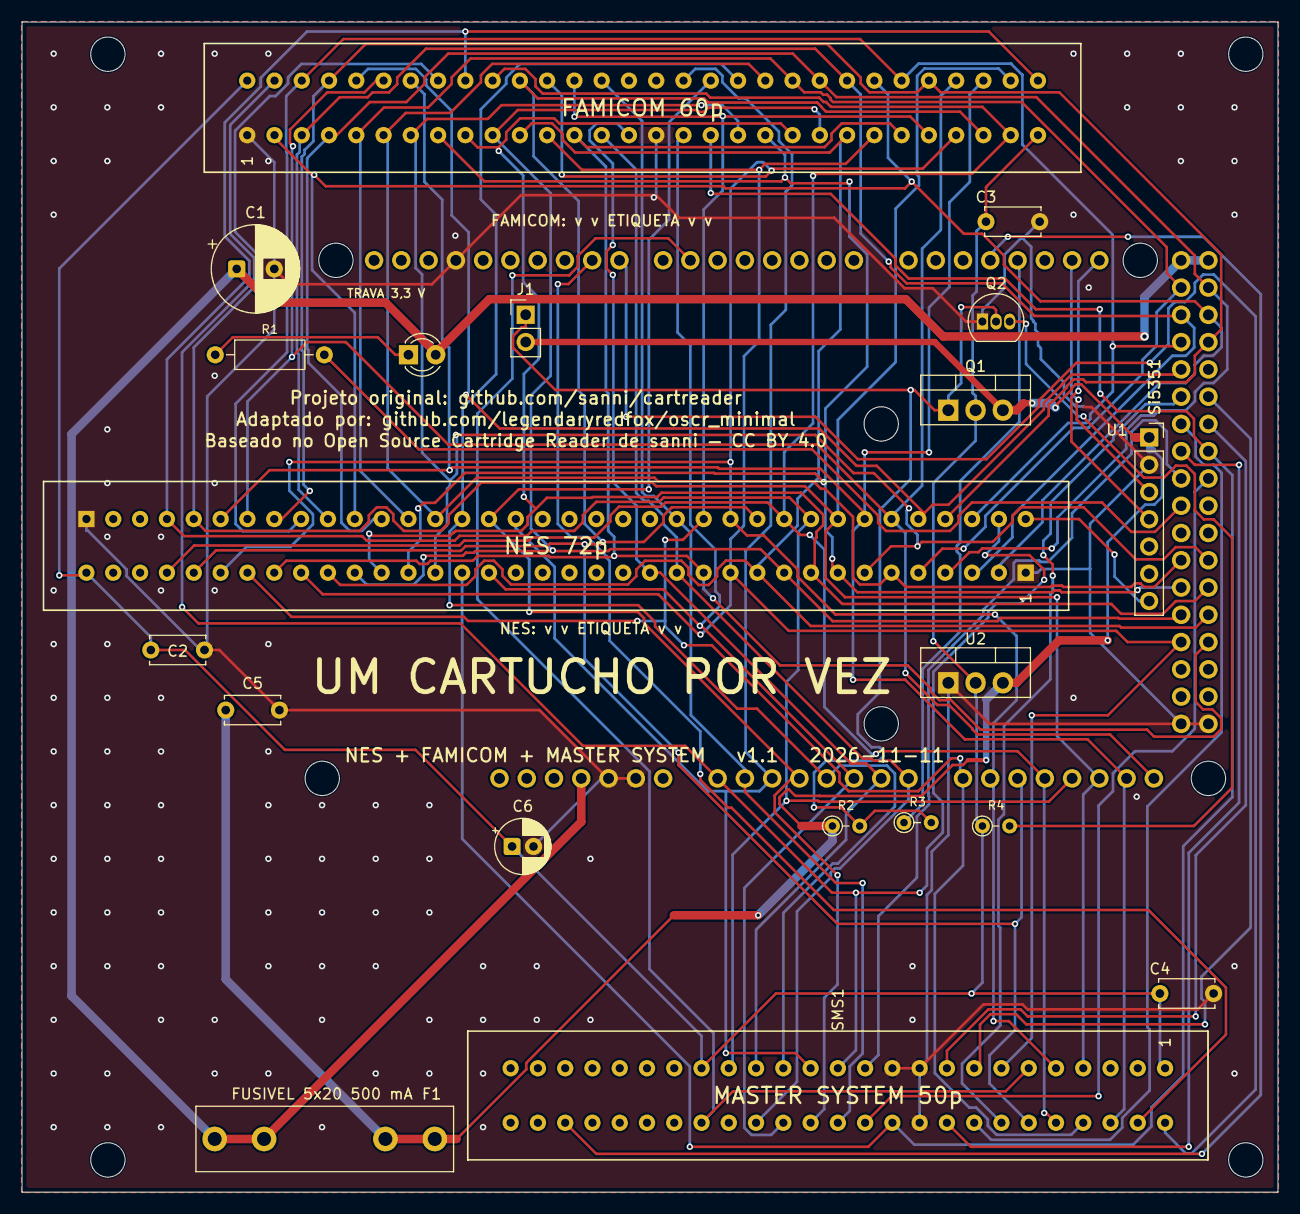
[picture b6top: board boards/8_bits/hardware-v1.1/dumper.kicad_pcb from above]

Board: 2 copper layers, 117.0 x 109.0 mm, 25 parts (0 on the bottom side), 55 nets.

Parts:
A1: Mega2560_R3_Shield
C1: 470u/16V; CP_Radial_D8.0mm_P3.50mm
C2, C3, C4, C5: 100n; C_Disc_D5.0mm_W2.5mm_P5.00mm
C6: 10u/16V; CP_Radial_D5.0mm_P2.00mm
D1: LED 3mm; LED_D3.0mm
F1: Fusivel 5x20 500mA; Fuseholder_Littelfuse_100_series_5x20mm
FC1: FC_Slot
J1: TRAVA 3,3 V; PinHeader_1x02_P2.54mm_Vertical
MH1, MH2, MH3, MH4: MountingHole_3.2mm; MountingHole_3.2mm_M3
NES1: NES_Slot
Q1: IRF9540N; TO-220-3_Vertical
Q2: 2N7000; TO-92_Inline
R1: 220R; R_Axial_DIN0207_L6.3mm_D2.5mm_P10.16mm_Horizontal
R2: 100k; R_Axial_DIN0204_L3.6mm_D1.6mm_P2.54mm_Vertical
R3: 1k; R_Axial_DIN0204_L3.6mm_D1.6mm_P2.54mm_Vertical
R4: 220R; R_Axial_DIN0204_L3.6mm_D1.6mm_P2.54mm_Vertical
SMS1: SMS_Slot
U1: Si5351_Module; PinSocket_1x07_P2.54mm_Vertical
U2: LD1117V33; TO-220-3_Vertical

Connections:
+5V: A1.5V1, A1.5V3, A1.5V4, C1.1, D1.2, F1.1
+5V_CART: C5.1, F1.2, J1.2, Q1.3, R2.1, U1.1, U2.3
/A0: A1.A0, FC1.32, NES1.38, SMS1.25
/A1: A1.A1, FC1.44, NES1.50, SMS1.26
/A2: A1.A2, FC1.47, NES1.56, SMS1.27
/A3: A1.A3, FC1.48, NES1.57, SMS1.28
/A4: A1.A4, FC1.49, NES1.58, SMS1.29
/A5: A1.A5, FC1.17, NES1.21, SMS1.30
/A6: A1.A6, FC1.15, NES1.15, SMS1.31
/A7: A1.A7, FC1.14, NES1.14, SMS1.32
/A8: A1.A8, FC1.26, FC1.43, NES1.30, NES1.49, SMS1.8
/A9: A1.A9, FC1.27, FC1.42, NES1.31, NES1.48, SMS1.9
/A10: A1.A10, FC1.28, FC1.41, NES1.32, NES1.47, SMS1.12
/A11: A1.A11, FC1.29, FC1.40, NES1.33, NES1.46, SMS1.10
/A12: A1.A12, FC1.39, FC1.60, NES1.45, NES1.69, SMS1.33
/A13: A1.A13, FC1.38, FC1.59, NES1.44, NES1.68, SMS1.7
/A14: A1.A14, FC1.37, FC1.58, NES1.43, NES1.67, SMS1.6
/A15: A1.A15, FC1.36, FC1.57, NES1.42, NES1.66
/CLK0: NES1.37, U1.7
/D6: A1.D6, SMS1.11, SMS1.36
/D8: A1.D8, SMS1.2
/D9: A1.D9, SMS1.4
/D17: A1.D17, SMS1.46
/D22: A1.D22, FC1.5, FC1.51, NES1.5, NES1.60
/D23: A1.D23, FC1.4, FC1.52, NES1.4, NES1.61
/D24: A1.D24, FC1.3, FC1.53, NES1.3, NES1.63
/D25: A1.D25, FC1.2, FC1.54, NES1.2, NES1.62
/D26: A1.D26, FC1.33, FC1.55, NES1.39, NES1.64
/D27: A1.D27, FC1.34, FC1.56, NES1.40, NES1.65
/D28: A1.D28, FC1.35, NES1.41
/D30: A1.D30, SMS1.14
/D31: A1.D31, SMS1.15
/D32: A1.D32, SMS1.16
/D33: A1.D33, SMS1.17
/D34: A1.D34, SMS1.18
/D35: A1.D35, FC1.18, NES1.22, SMS1.22
/D36: A1.D36, SMS1.23
/D37: A1.D37, SMS1.24
/D42: A1.D42, FC1.6, FC1.50, NES1.6, NES1.59
/D43: A1.D43, FC1.7, FC1.19, NES1.7, NES1.23
/D44: A1.D44, FC1.8, FC1.20, NES1.8, NES1.24
/D45: A1.D45, FC1.9, FC1.21, NES1.9, NES1.25
/D46: A1.D46, FC1.10, FC1.22, NES1.10, NES1.26
/D47: A1.D47, FC1.11, FC1.23, NES1.11, NES1.27
/D48: A1.D48, FC1.12, FC1.24, NES1.12, NES1.28, SMS1.13
/D49: A1.D49, FC1.13, FC1.25, NES1.13, NES1.29
/VSEL_EN: A1.D18, R3.1
/VSEL_G: J1.1, Q1.1, Q2.2, R2.2, R3.2
GND: A1.GND1, A1.GND2, A1.GND3, A1.GND5, A1.GND6, C1.2, C2.2, C3.2, C4.2, C5.2, C6.2, FC1.1, FC1.16, NES1.1, NES1.72, Q2.1, SMS1.19, SMS1.20, SMS1.21, U1.2, U2.1
unnamed: A1.D38, R1.2
unnamed: D1.1, R1.1
unnamed: Q2.3, R4.2
unnamed: A1.D21, U1.4
unnamed: A1.D20, U1.3
VCC_CART: C2.1, C3.1, C4.1, C6.1, FC1.30, FC1.31, NES1.36, Q1.2, R4.1, SMS1.1, SMS1.35, U2.2

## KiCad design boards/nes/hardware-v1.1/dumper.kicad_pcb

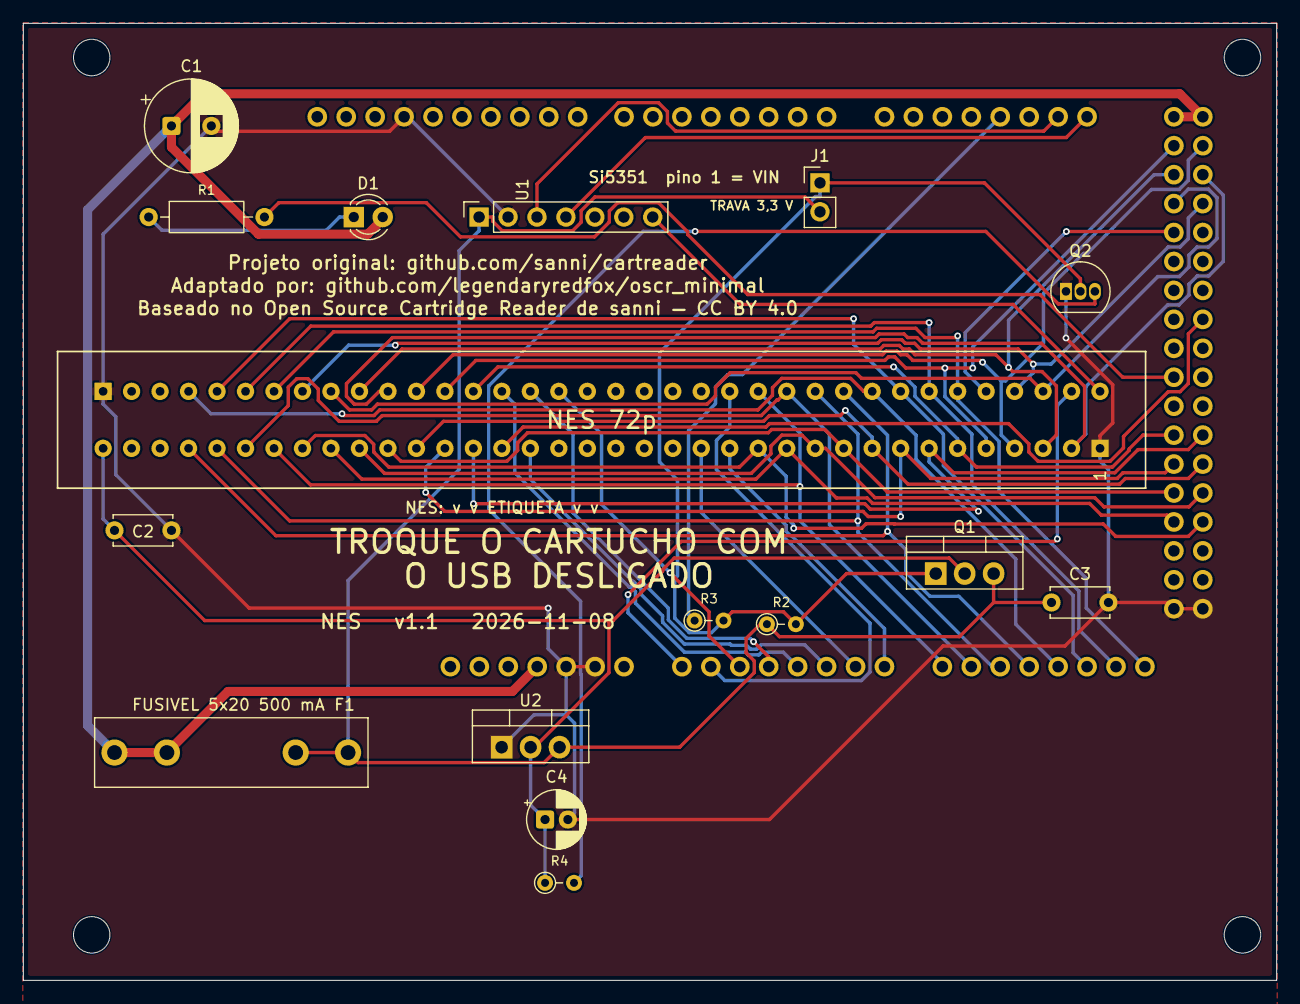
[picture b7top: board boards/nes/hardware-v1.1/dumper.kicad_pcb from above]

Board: 2 copper layers, 110.0 x 84.0 mm, 21 parts (0 on the bottom side), 44 nets.

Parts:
A1: Mega2560_R3_Shield
C1: 470u/16V; CP_Radial_D8.0mm_P3.50mm
C2, C3: 100n; C_Disc_D5.0mm_W2.5mm_P5.00mm
C4: 10u/16V; CP_Radial_D5.0mm_P2.00mm
D1: LED 3mm; LED_D3.0mm
F1: Fusivel 5x20 500mA; Fuseholder_Littelfuse_100_series_5x20mm
J1: TRAVA 3,3 V; PinHeader_1x02_P2.54mm_Vertical
MH1, MH2, MH3, MH4: MountingHole_3.2mm; MountingHole_3.2mm_M3
NES1: NES_Slot
Q1: IRF9540N; TO-220-3_Vertical
Q2: 2N7000; TO-92_Inline
R1: 220R; R_Axial_DIN0207_L6.3mm_D2.5mm_P10.16mm_Horizontal
R2: 100k; R_Axial_DIN0204_L3.6mm_D1.6mm_P2.54mm_Vertical
R3: 1k; R_Axial_DIN0204_L3.6mm_D1.6mm_P2.54mm_Vertical
R4: 220R; R_Axial_DIN0204_L3.6mm_D1.6mm_P2.54mm_Vertical
U1: Si5351_Module; PinSocket_1x07_P2.54mm_Vertical
U2: LD1117V33; TO-220-3_Vertical

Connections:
+5V: A1.5V1, A1.5V3, A1.5V4, C1.1, D1.2, F1.1
+5V_CART: C3.1, F1.2, J1.2, Q1.3, R2.1, U1.1, U2.3
/A0: A1.A0, NES1.38
/A1: A1.A1, NES1.50
/A2: A1.A2, NES1.56
/A3: A1.A3, NES1.57
/A4: A1.A4, NES1.58
/A5: A1.A5, NES1.21
/A6: A1.A6, NES1.15
/A7: A1.A7, NES1.14
/A8: A1.A8, NES1.30, NES1.49
/A9: A1.A9, NES1.31, NES1.48
/A10: A1.A10, NES1.32, NES1.47
/A11: A1.A11, NES1.33, NES1.46
/A12: A1.A12, NES1.45, NES1.69
/A13: A1.A13, NES1.44, NES1.68
/A14: A1.A14, NES1.43, NES1.67
/A15: A1.A15, NES1.42, NES1.66
/CLK0: NES1.37, U1.7
/D22: A1.D22, NES1.5, NES1.60
/D23: A1.D23, NES1.4, NES1.61
/D24: A1.D24, NES1.3, NES1.63
/D25: A1.D25, NES1.2, NES1.62
/D26: A1.D26, NES1.39, NES1.64
/D27: A1.D27, NES1.40, NES1.65
/D28: A1.D28, NES1.41
/D35: A1.D35, NES1.22
/D42: A1.D42, NES1.6, NES1.59
/D43: A1.D43, NES1.7, NES1.23
/D44: A1.D44, NES1.8, NES1.24
/D45: A1.D45, NES1.9, NES1.25
/D46: A1.D46, NES1.10, NES1.26
/D47: A1.D47, NES1.11, NES1.27
/D48: A1.D48, NES1.12, NES1.28
/D49: A1.D49, NES1.13, NES1.29
/VSEL_EN: A1.D18, R3.1
/VSEL_G: J1.1, Q1.1, Q2.2, R2.2, R3.2
GND: A1.GND1, A1.GND2, A1.GND3, A1.GND5, A1.GND6, C1.2, C2.2, C3.2, C4.2, NES1.1, NES1.72, Q2.1, U1.2, U2.1
unnamed: A1.D38, R1.2
unnamed: D1.1, R1.1
unnamed: Q2.3, R4.2
unnamed: A1.D21, U1.4
unnamed: A1.D20, U1.3
VCC_CART: C2.1, C4.1, NES1.36, Q1.2, R4.1, U2.2

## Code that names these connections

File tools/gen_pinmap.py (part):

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    w("\n## Placa principal — o que o HW5 liga além dos slots (referência)\n")
    w("| item | pino Arduino | fonte |\n|---|---|---|")
    w("| Si5351 SDA / SCL | D20 (PD1) / D21 (PD0) | sch main J7.3/J7.4 + ods |")
    w("| Si5351 CLK0 / CLK1 / CLK2 | 3 saídas do Si5351 (não vão ao Mega); CLK0→SNES 21.477MHz (pino 1), CLK1→SNES CPU clock (57), CLK2→CIC clock (56) e PIC pino 2 | sch |")
    w("| LED de status (cátodo via 220Ω, ânodo em VCC; **ativo em nível baixo**) | D38 (PD7) | sch main D1/R1 + fw `statusLED()` |")
    w("| Pull-up 1kΩ VCC→D7 (linha /IRQ do SNES) | D7 (PH4) | sch six_slot R1 + ods `D7 (1K Pullup)` |")
    w("| Reset do Mega | RESET → J4.35 (adaptadores não usam) | sch main |\n")
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    for net, nodes in pic.items():
        for r, p, fn in nodes:
            if r == "PIC12F629": pm[p] = net
    tgt = {"VCC": "5V", "GND": "GND", "CLK2": "Si5351 CLK2 (mesma net do SNES pino 56)",
           "D40": "Mega D40 (PG1) — Reset In", "D41": "Mega D41 (PG0) — Reset Out Host",
           "CIC RESET": "SNES slot pino 25 (CIC_in_data p7)",
           "CIC DATA 1": "SNES slot pino 24 (CIC_out_data p1)",
           "CIC DATA 0": "SNES slot pino 55 (CIC_data_out p2)"}
    for p in sorted(pm, key=int):
        w(f"| {p} | {pm[p]} | {tgt.get(pm[p], '?')} | sch(PIC_adapter + six_slot JCIC1) + ods(snesCIC) + fw SNES.ino (PG0/PG1) |")
    w("\nNota: o PIC12F629 usa a pinagem do `JCIC1` (1=VCC, 2=CLK2, 3=D41, 4=D40, 5=RESET, 6=DATA1, 7=DATA0, 8=GND).\n")
    w("## Pinos do slot sem ligação no OSCR (mantidos sem ligação)\n")
    w("- SNES: pino 31 (Left Audio), pino 62 (Right Audio).")
    w("- NES: `EXP_0..EXP_9` (16-20, 51-55), `Security1..4` (70, 71, 34, 35).")
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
